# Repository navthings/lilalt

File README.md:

lilalt

beeping altimeter for my first rocket. attiny412 + bmp280, beeps the max altitude after landing. 8-pin grant.

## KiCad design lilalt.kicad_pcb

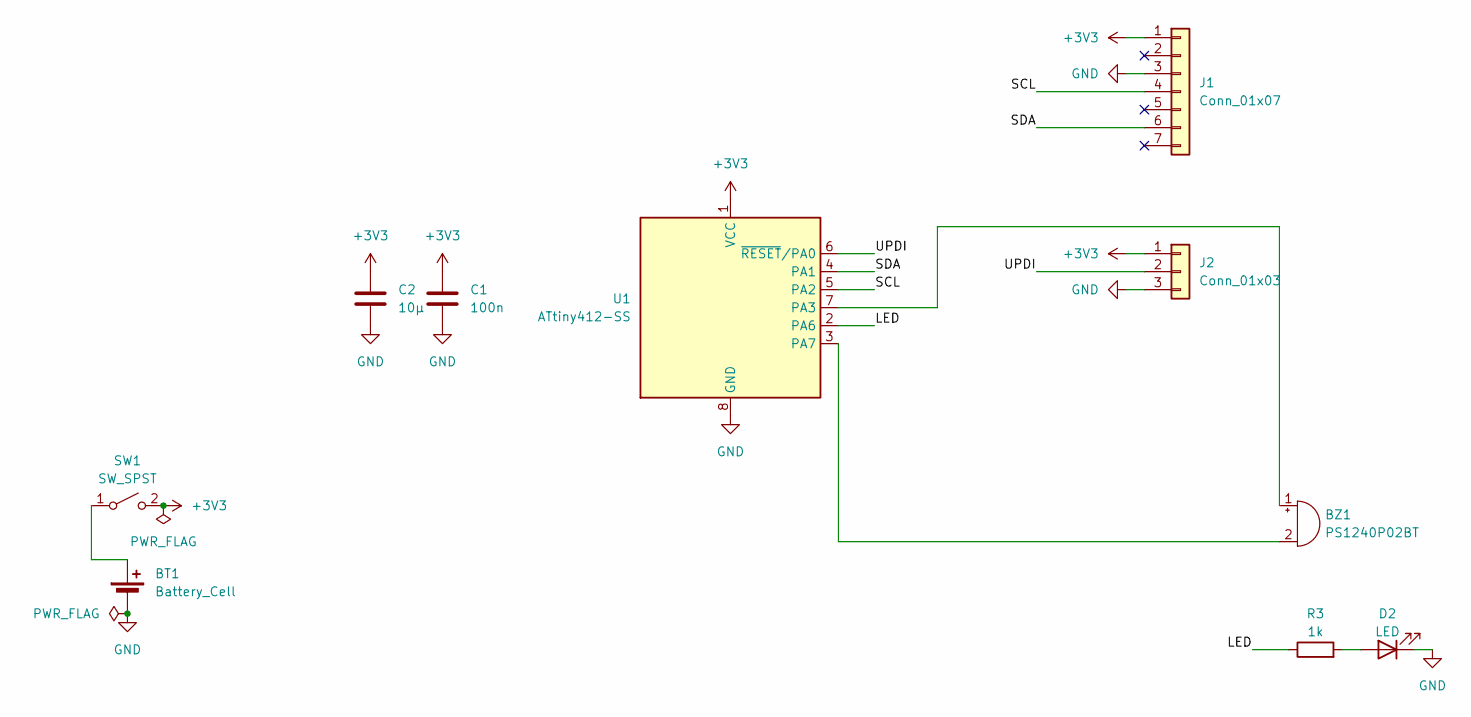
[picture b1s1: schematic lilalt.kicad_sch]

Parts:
BT1: Battery_Cell; BatteryHolder_Keystone_103_1x20mm; MPN 103; DigiKey 36-103-ND
BZ1: PS1240P02BT; Buzzer_TDK_PS1240P02BT_D12.2mm_H6.5mm
C1: 100n; C_Disc_D5.0mm_W2.5mm_P5.00mm; MPN C322C104K1R5TA; DigiKey 399-4328-ND
C2: 10µ; C_Disc_D5.0mm_W2.5mm_P5.00mm; MPN C322C106K3R5TA; DigiKey 399-13968-ND
D2: LED; LED_D3.0mm; MPN WP7104LID; DigiKey 754-1245-ND
J1: Conn_01x07; PinHeader_1x07_P2.54mm_Vertical; MPN 2651 (BMP280 breakout, header included); DigiKey 1528-1358-ND
J2: Conn_01x03; PinHeader_1x03_P2.54mm_Vertical; MPN PREC003SAAN-RC; DigiKey S1012EC-03-ND
R3: 1k; R_Axial_DIN0207_L6.3mm_D2.5mm_P10.16mm_Horizontal; MPN CF14JT1K00; DigiKey CF14JT1K00CT-ND
SW1: SW_SPST; SW_Slide_SPDT_Straight_CK_OS102011MS2Q; MPN OS102011MS2QN1; DigiKey CKN9565-ND
U1: ATtiny412-SS; SOIC-8_3.9x4.9mm_P1.27mm; MPN ATTINY412-SSNR; DigiKey ATTINY412-SSNRCT-ND

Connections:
+3V3: C1.1, C2.1, J1.1, J2.1, SW1.2 (B), U1.1 (VCC)
/LED: R3.1, U1.2 (PA6)
/SCL: J1.4, U1.5 (PA2)
/SDA: J1.6, U1.4 (PA1)
/UPDI: J2.2, U1.6 (~RESET/PA0)
GND: BT1.2 (-), C1.2, C2.2, D2.1 (K), J1.3, J2.3, U1.8 (GND)
unnamed: BT1.1 (+), SW1.1 (A)
unnamed: BZ1.1 (+), U1.7 (PA3)
unnamed: BZ1.2 (-), U1.3 (PA7)
unnamed: D2.2 (A), R3.2

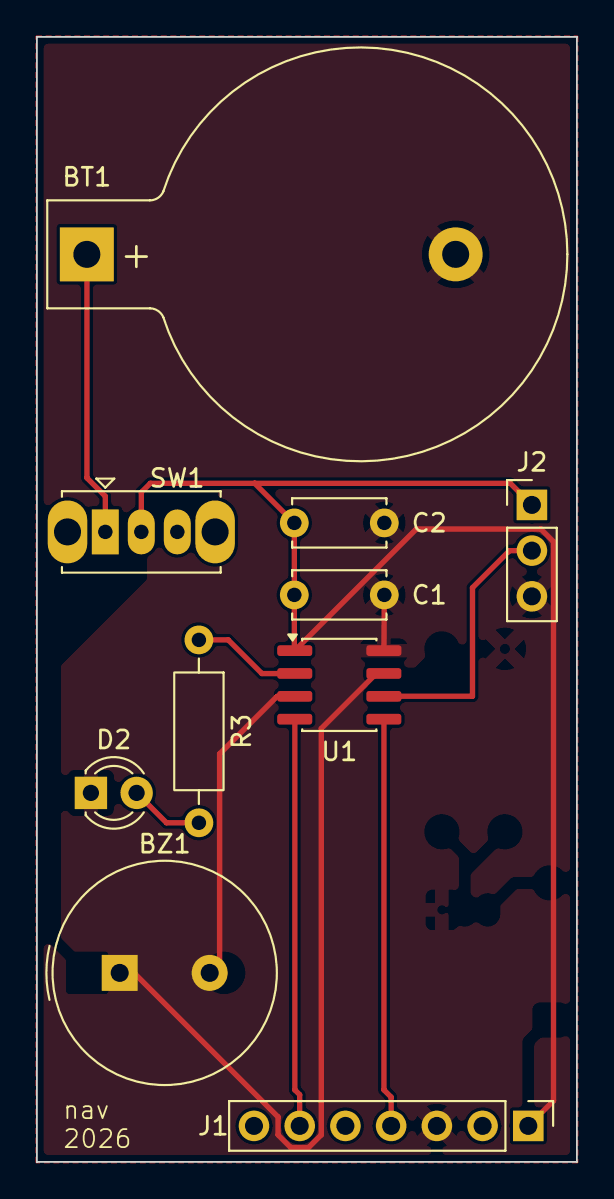
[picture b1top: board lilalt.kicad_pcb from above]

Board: 2 copper layers, 30.0 x 62.5 mm, 10 parts (0 on the bottom side), 10 nets.
